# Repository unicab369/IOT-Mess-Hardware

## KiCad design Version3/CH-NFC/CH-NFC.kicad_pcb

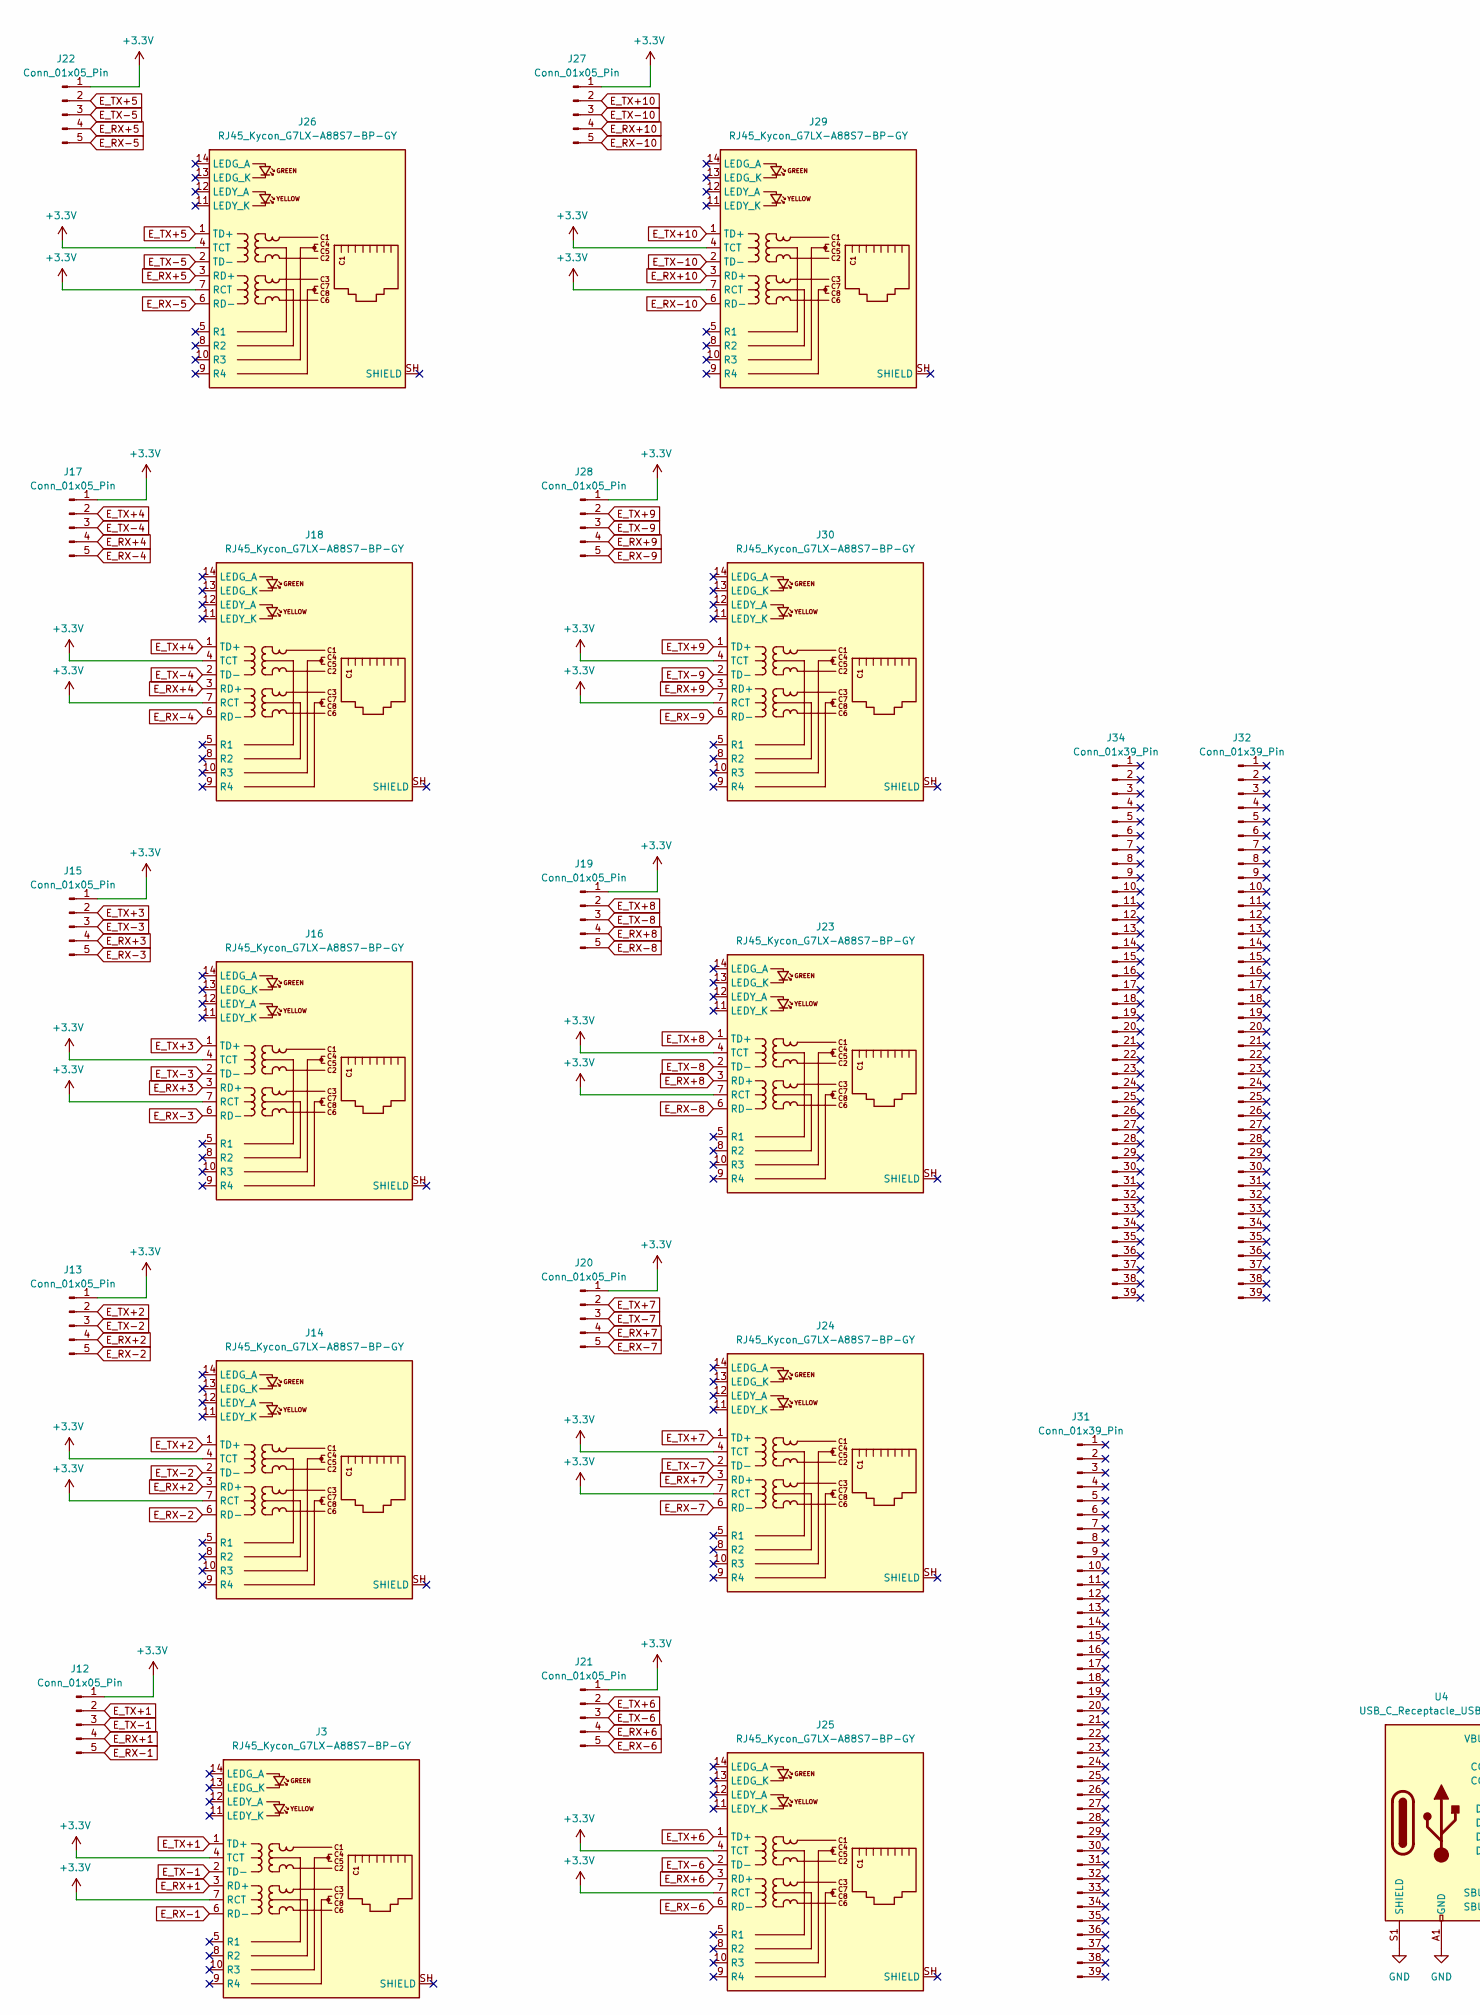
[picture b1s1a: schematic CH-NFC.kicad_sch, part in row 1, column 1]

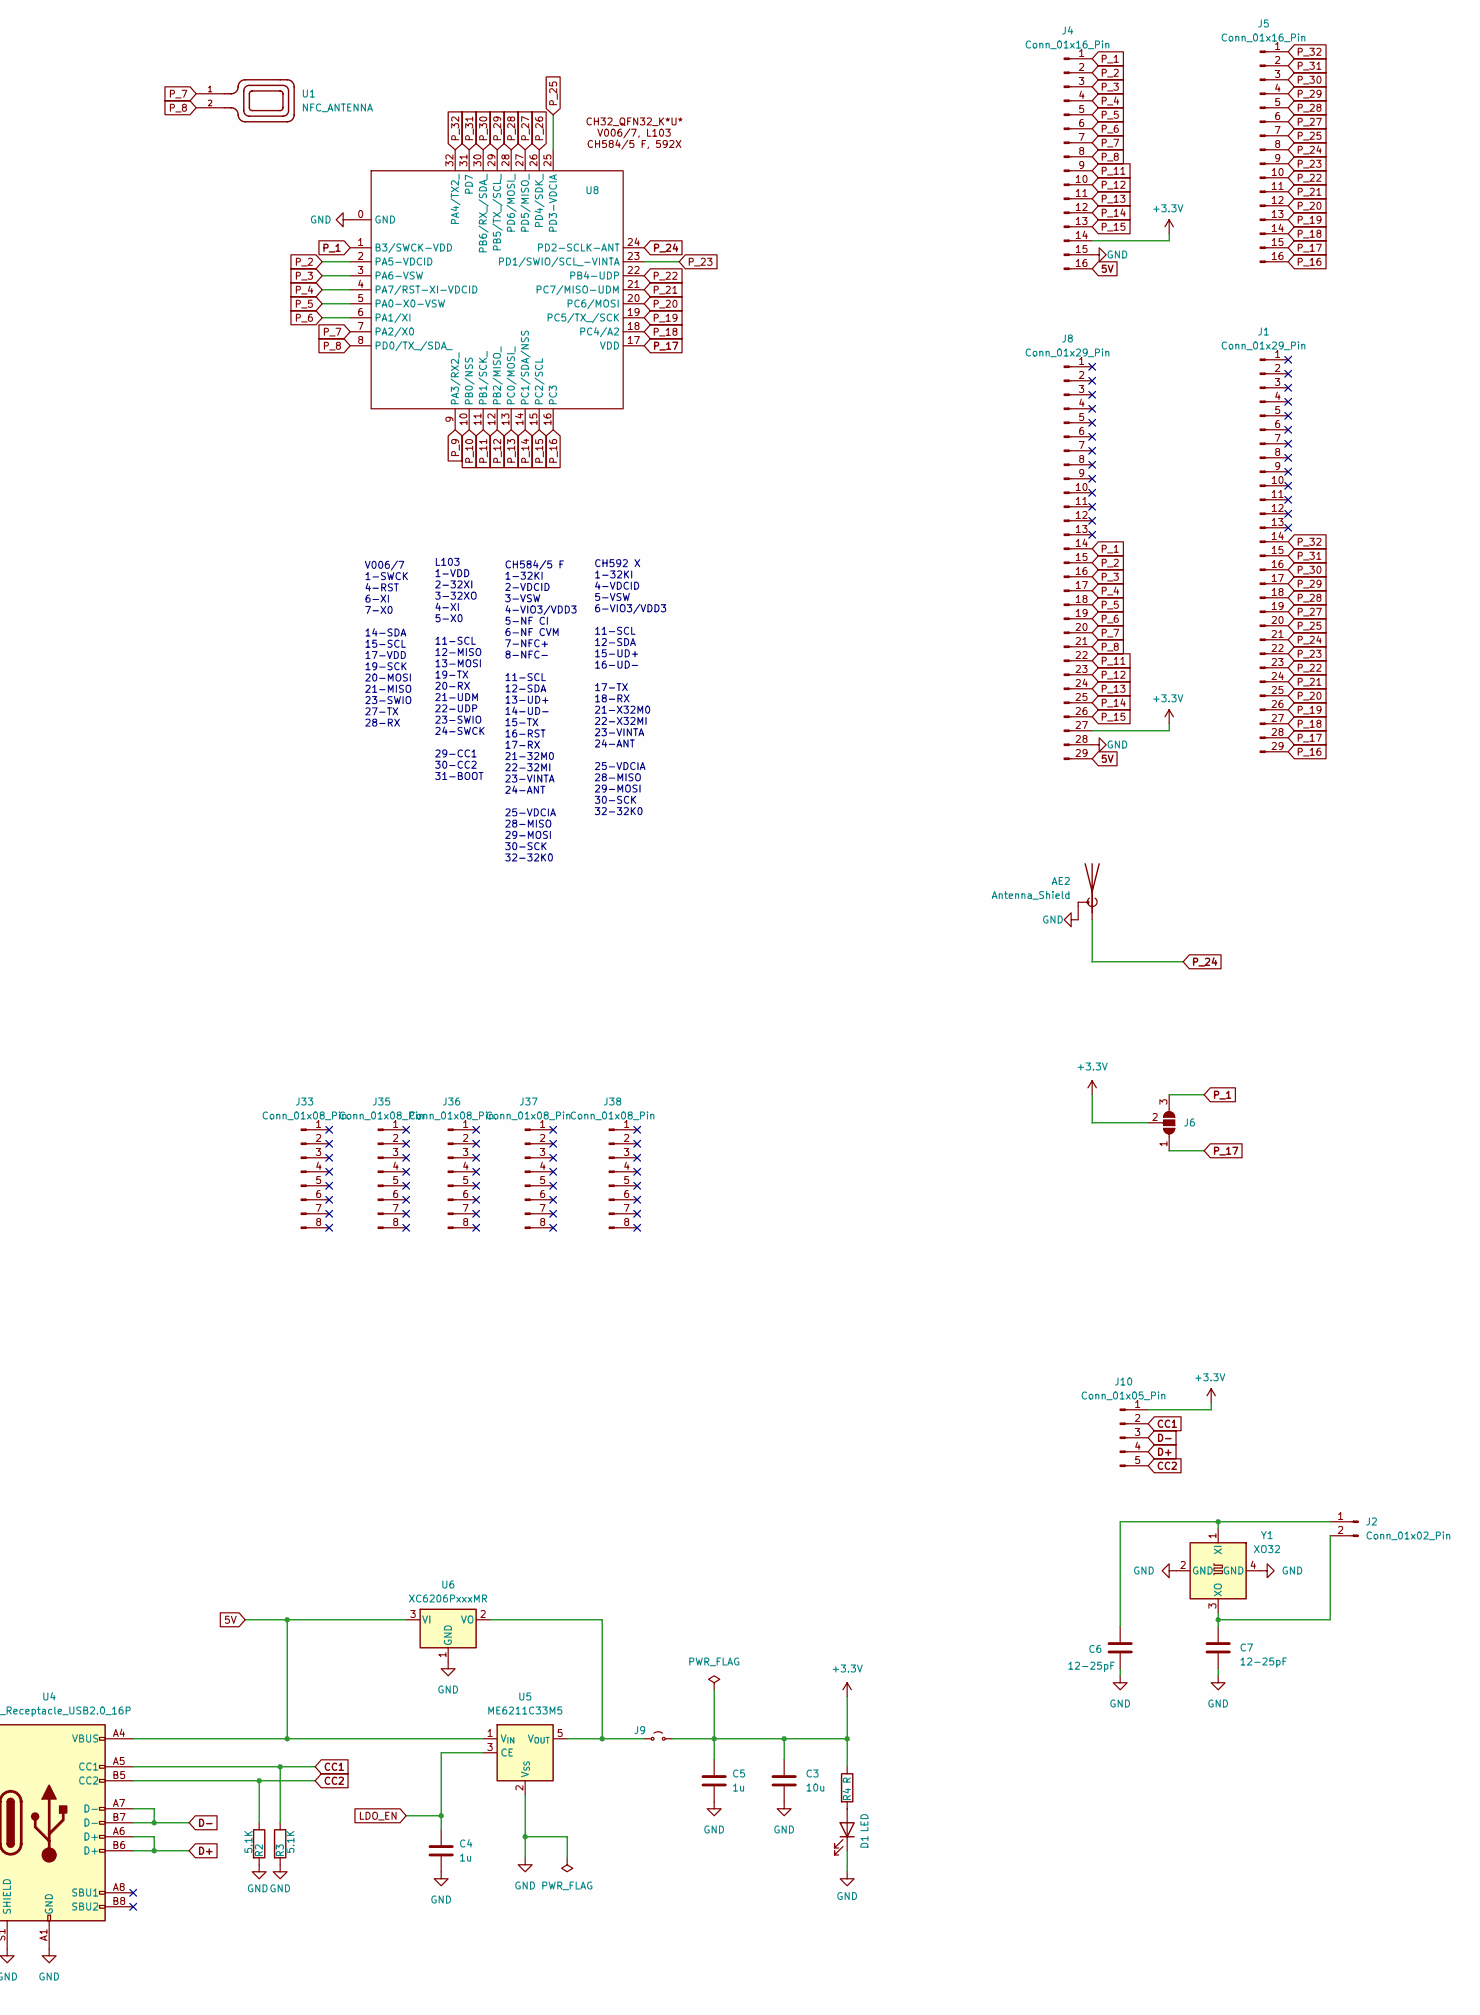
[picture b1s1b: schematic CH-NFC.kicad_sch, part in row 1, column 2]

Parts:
AE2: Antenna_Shield; Texas_SWRA117D_2.4GHz_Left
C3: 10u; C_0603_1608Metric
C4, C5: 1u; C_0603_1608Metric
C6, C7: 12-25pF; C_0603_1608Metric
D1: LED; LED_0603_1608Metric
J1, J8: Conn_01x29_Pin; PinHeader_1x29_P2.54mm_Vertical
J2: Conn_01x02_Pin; PinHeader_1x02_P1.27mm_Vertical
J3, J14, J16, J18, J23, J24, J25, J26, J29, J30: RJ45_Kycon_G7LX-A88S7-BP-GY; RJ45_Kycon_G7LX-A88S7-BP-xx_Horizontal
J4, J5: Conn_01x16_Pin; PinHeader_1x16_P2.54mm_Vertical
J6: Jumper; Jumper-3_P1.3mm_Open_RoundedPad1.0x1.5mm
J9: Jumper_2; Jumpper-triangle
J10: Conn_01x05_Pin; PinHeader_1x05_P1.27mm_Vertical
J12, J13, J15, J17, J19, J20, J21, J22, J27, J28: Conn_01x05_Pin; PinHeader_1x05_P2.54mm_Vertical
J31, J32, J34: Conn_01x39_Pin; PinHeader_1x39_P2.54mm_Vertical
J33, J35, J36, J37, J38: Conn_01x08_Pin; PinHeader_1x08_P2.54mm_Vertical
R2, R3: 5.1K; R_0603_1608Metric
R4: R; R_0603_1608Metric
U1: NFC_ANTENNA; NFC_ANT
U4: USB_C_Receptacle_USB2.0_16P; USB_C_Receptacle_HRO_TYPE-C-31-M-12
U5: ME6211C33M5; SOT-23-5
U6: XC6206PxxxMR; SOT-23-3
U8: QFN-32-1EP_4x4mm_P0.4mm_EP2.65x2.65mm_ThermalVias
Y1: XO32; Oscillator_SMD_EuroQuartz_XO32-4Pin_3.2x2.5mm

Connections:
5V: J4.16, J8.29, U4.A4 (VBUS), U4.A9 (VBUS), U4.B4 (VBUS), U4.B9 (VBUS), U5.1 (V_{IN}), U6.3 (VI)
+3.3V: C3.1, C5.1, J3.4 (TCT), J3.7 (RCT), J4.14, J6.2 (C), J8.27, J9.2 (B), J10.1, J12.1, J13.1, J14.4 (TCT), J14.7 (RCT), J15.1, J16.4 (TCT), J16.7 (RCT), J17.1, J18.4 (TCT), J18.7 (RCT), J19.1, J20.1, J21.1, J22.1, J23.4 (TCT), J23.7 (RCT), J24.4 (TCT), J24.7 (RCT), J25.4 (TCT), J25.7 (RCT), J26.4 (TCT), J26.7 (RCT), J27.1, J28.1, J29.4 (TCT), J29.7 (RCT), J30.4 (TCT), J30.7 (RCT), R4.1
CC1: J10.2, R3.1, U4.A5 (CC1)
CC2: J10.5, R2.1, U4.B5 (CC2)
D+: J10.4, U4.A6 (D+), U4.B6 (D+)
D-: J10.3, U4.A7 (D-), U4.B7 (D-)
E_RX+1: J3.3 (RD+), J12.4
E_RX+2: J13.4, J14.3 (RD+)
E_RX+3: J15.4, J16.3 (RD+)
E_RX+4: J17.4, J18.3 (RD+)
E_RX+5: J22.4, J26.3 (RD+)
E_RX+6: J21.4, J25.3 (RD+)
E_RX+7: J20.4, J24.3 (RD+)
E_RX+8: J19.4, J23.3 (RD+)
E_RX+9: J28.4, J30.3 (RD+)
E_RX+10: J27.4, J29.3 (RD+)
E_RX-1: J3.6 (RD-), J12.5
E_RX-2: J13.5, J14.6 (RD-)
E_RX-3: J15.5, J16.6 (RD-)
E_RX-4: J17.5, J18.6 (RD-)
E_RX-5: J22.5, J26.6 (RD-)
E_RX-6: J21.5, J25.6 (RD-)
E_RX-7: J20.5, J24.6 (RD-)
E_RX-8: J19.5, J23.6 (RD-)
E_RX-9: J28.5, J30.6 (RD-)
E_RX-10: J27.5, J29.6 (RD-)
E_TX+1: J3.1 (TD+), J12.2
E_TX+2: J13.2, J14.1 (TD+)
E_TX+3: J15.2, J16.1 (TD+)
E_TX+4: J17.2, J18.1 (TD+)
E_TX+5: J22.2, J26.1 (TD+)
E_TX+6: J21.2, J25.1 (TD+)
E_TX+7: J20.2, J24.1 (TD+)
E_TX+8: J19.2, J23.1 (TD+)
E_TX+9: J28.2, J30.1 (TD+)
E_TX+10: J27.2, J29.1 (TD+)
E_TX-1: J3.2 (TD-), J12.3
E_TX-2: J13.3, J14.2 (TD-)
E_TX-3: J15.3, J16.2 (TD-)
E_TX-4: J17.3, J18.2 (TD-)
E_TX-5: J22.3, J26.2 (TD-)
E_TX-6: J21.3, J25.2 (TD-)
E_TX-7: J20.3, J24.2 (TD-)
E_TX-8: J19.3, J23.2 (TD-)
E_TX-9: J28.3, J30.2 (TD-)
E_TX-10: J27.3, J29.2 (TD-)
GND: AE2.2 (Shield), C3.2, C4.2, C5.2, C6.2, C7.2, D1.1 (K), J4.15, J8.28, R2.2, R3.2, U4.A1 (GND), U4.A12 (GND), U4.B1 (GND), U4.B12 (GND), U4.S1 (SHIELD), U5.2 (V_{SS}), U6.1 (GND), U8.0 (GND), Y1.2 (GND), Y1.4 (GND)
LDO_EN: C4.1, U5.3 (CE)
unnamed: D1.2 (A), R4.2
unnamed: C6.1, J2.1, Y1.1 (XI)
unnamed: C7.1, J2.2, Y1.3 (XO)
unnamed: J9.1 (A), U5.5 (V_{OUT}), U6.2 (VO)
P_1: J4.1, J6.3 (B), J8.14, U8.1 (B3/SWCK-VDD)
P_2: J4.2, J8.15, U8.2 (PA5-VDCID)
P_3: J4.3, J8.16, U8.3 (PA6-VSW)
P_4: J4.4, J8.17, U8.4 (PA7/RST-XI-VDCID)
P_5: J4.5, J8.18, U8.5 (PA0-X0-VSW)
P_6: J4.6, J8.19, U8.6 (PA1/XI)
P_7: J4.7, J8.20, U1.1, U8.7 (PA2/X0)
P_8: J4.8, J8.21, U1.2, U8.8 (PD0/TX_/SDA_)
P_9: U8.9 (PA3/RX2_)
P_10: U8.10 (PB0/NSS)
P_11: J4.9, J8.22, U8.11 (PB1/SCK_)
P_12: J4.10, J8.23, U8.12 (PB2/MISO_)
P_13: J4.11, J8.24, U8.13 (PC0/MOSI_)
P_14: J4.12, J8.25, U8.14 (PC1/SDA/NSS)
P_15: J4.13, J8.26, U8.15 (PC2/SCL)
P_16: J1.29, J5.16, U8.16 (PC3)
P_17: J1.28, J5.15, J6.1 (A), U8.17 (VDD)
P_18: J1.27, J5.14, U8.18 (PC4/A2)
P_19: J1.26, J5.13, U8.19 (PC5/TX_/SCK)
P_20: J1.25, J5.12, U8.20 (PC6/MOSI)
P_21: J1.24, J5.11, U8.21 (PC7/MISO-UDM)
P_22: J1.23, J5.10, U8.22 (PB4-UDP)
P_23: J1.22, J5.9, U8.23 (PD1/SWIO/SCL_-VINTA)
P_24: AE2.1 (A), J1.21, J5.8, U8.24 (PD2-SCLK-ANT)
P_25: J1.20, J5.7, U8.25 (PD3-VDCIA)
P_26: U8.26 (PD4/SDK_)
P_27: J1.19, J5.6, U8.27 (PD5/MISO_)
P_28: J1.18, J5.5, U8.28 (PD6/MOSI_)
P_29: J1.17, J5.4, U8.29 (PB5/TX_/SCL_)
P_30: J1.16, J5.3, U8.30 (PB6/RX_/SDA_)
P_31: J1.15, J5.2, U8.31 (PD7)
P_32: J1.14, J5.1, U8.32 (PA4/TX2_)

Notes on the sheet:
V006/7 1-SWCK 4-RST 6-XI 7-X0 14-SDA 15-SCL 17-VDD 19-SCK 20-MOSI 21-MISO 23-SWIO 27-TX 28-RX
L103 1-VDD 2-32XI 3-32XO 4-XI 5-X0 11-SCL 12-MISO 13-MOSI 19-TX 20-RX 21-UDM 22-UDP 23-SWIO 24-SWCK 29-CC1 30-CC2 31-BOOT
CH592 X 1-32KI 4-VDCID 5-VSW 6-VIO3/VDD3 11-SCL 12-SDA 15-UD+ 16-UD- 17-TX 18-RX 21-X32M0 22-X32MI 23-VINTA 24-ANT 25-VDCIA 28-MISO 29-MOSI 30-SCK 32-32K0
CH584/5 F 1-32KI 2-VDCID 3-VSW 4-VIO3/VDD3 5-NF CI 6-NF CVM 7-NFC+ 8-NFC- 11-SCL 12-SDA 13-UD+ 14-UD- 15-TX 16-RST 17-RX 21-32M0 22-32MI 23-VINTA 24-ANT 25-VDCIA 28-MISO 29-MOSI 30-SCK 32-32K0

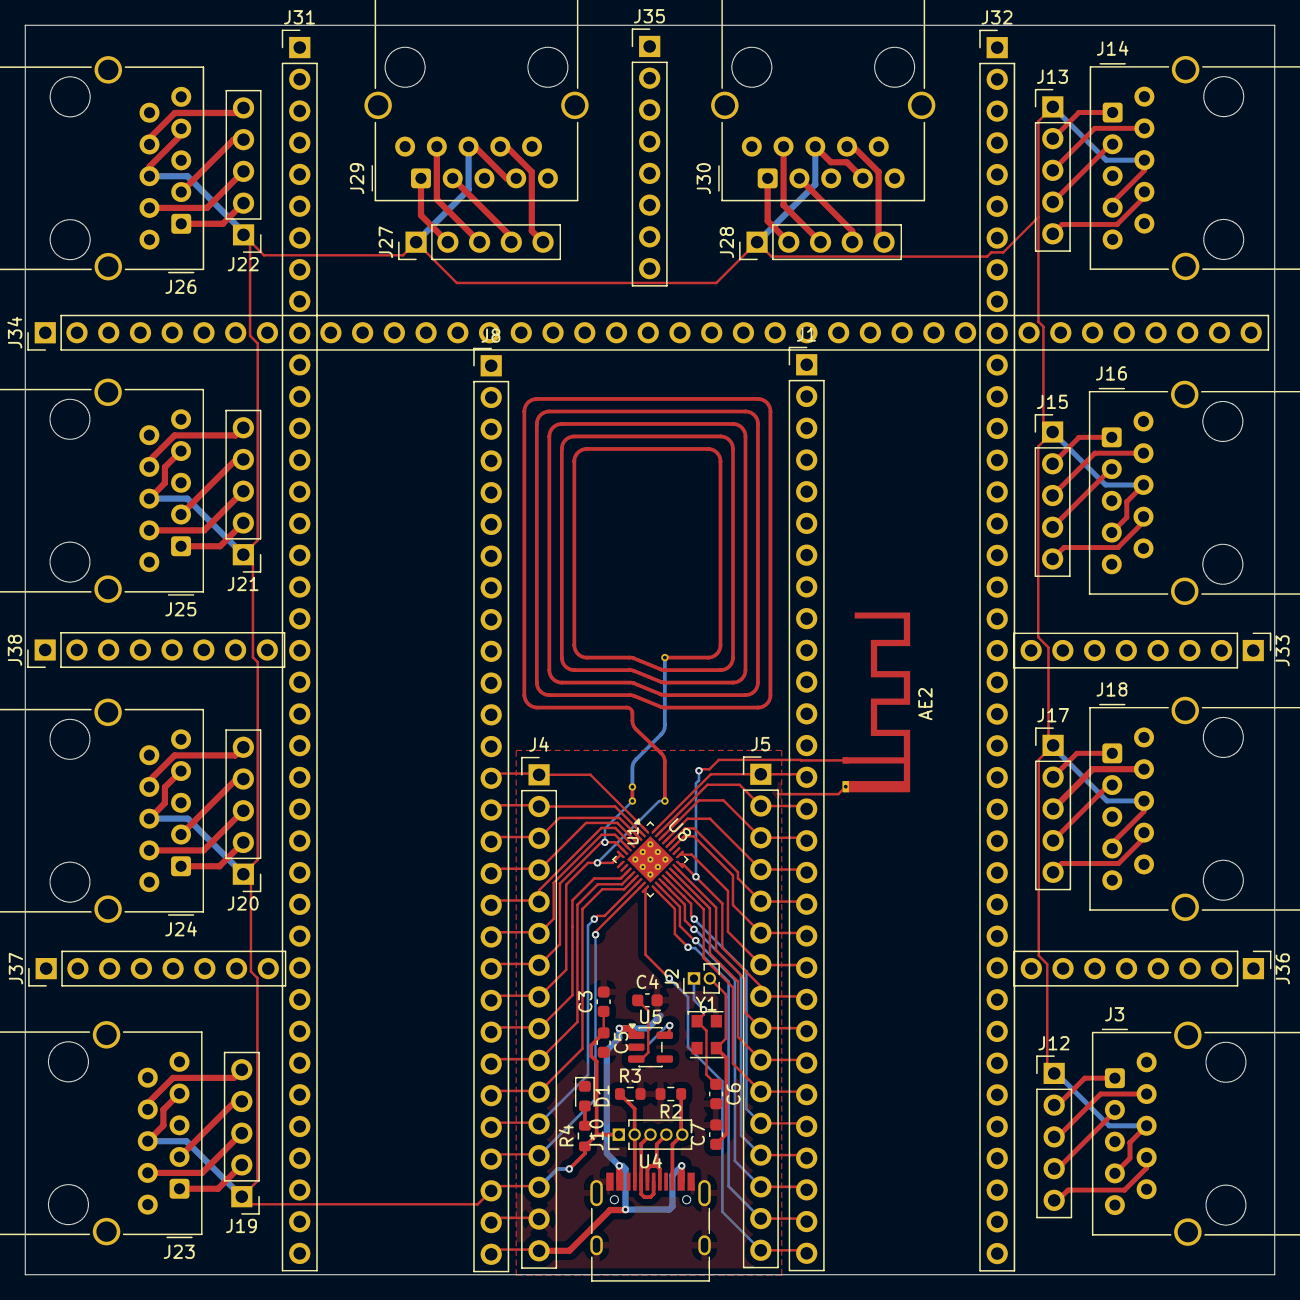
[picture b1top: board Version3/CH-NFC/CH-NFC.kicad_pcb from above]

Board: 2 copper layers, 100.0 x 100.0 mm, 50 parts (1 on the bottom side), 81 nets.

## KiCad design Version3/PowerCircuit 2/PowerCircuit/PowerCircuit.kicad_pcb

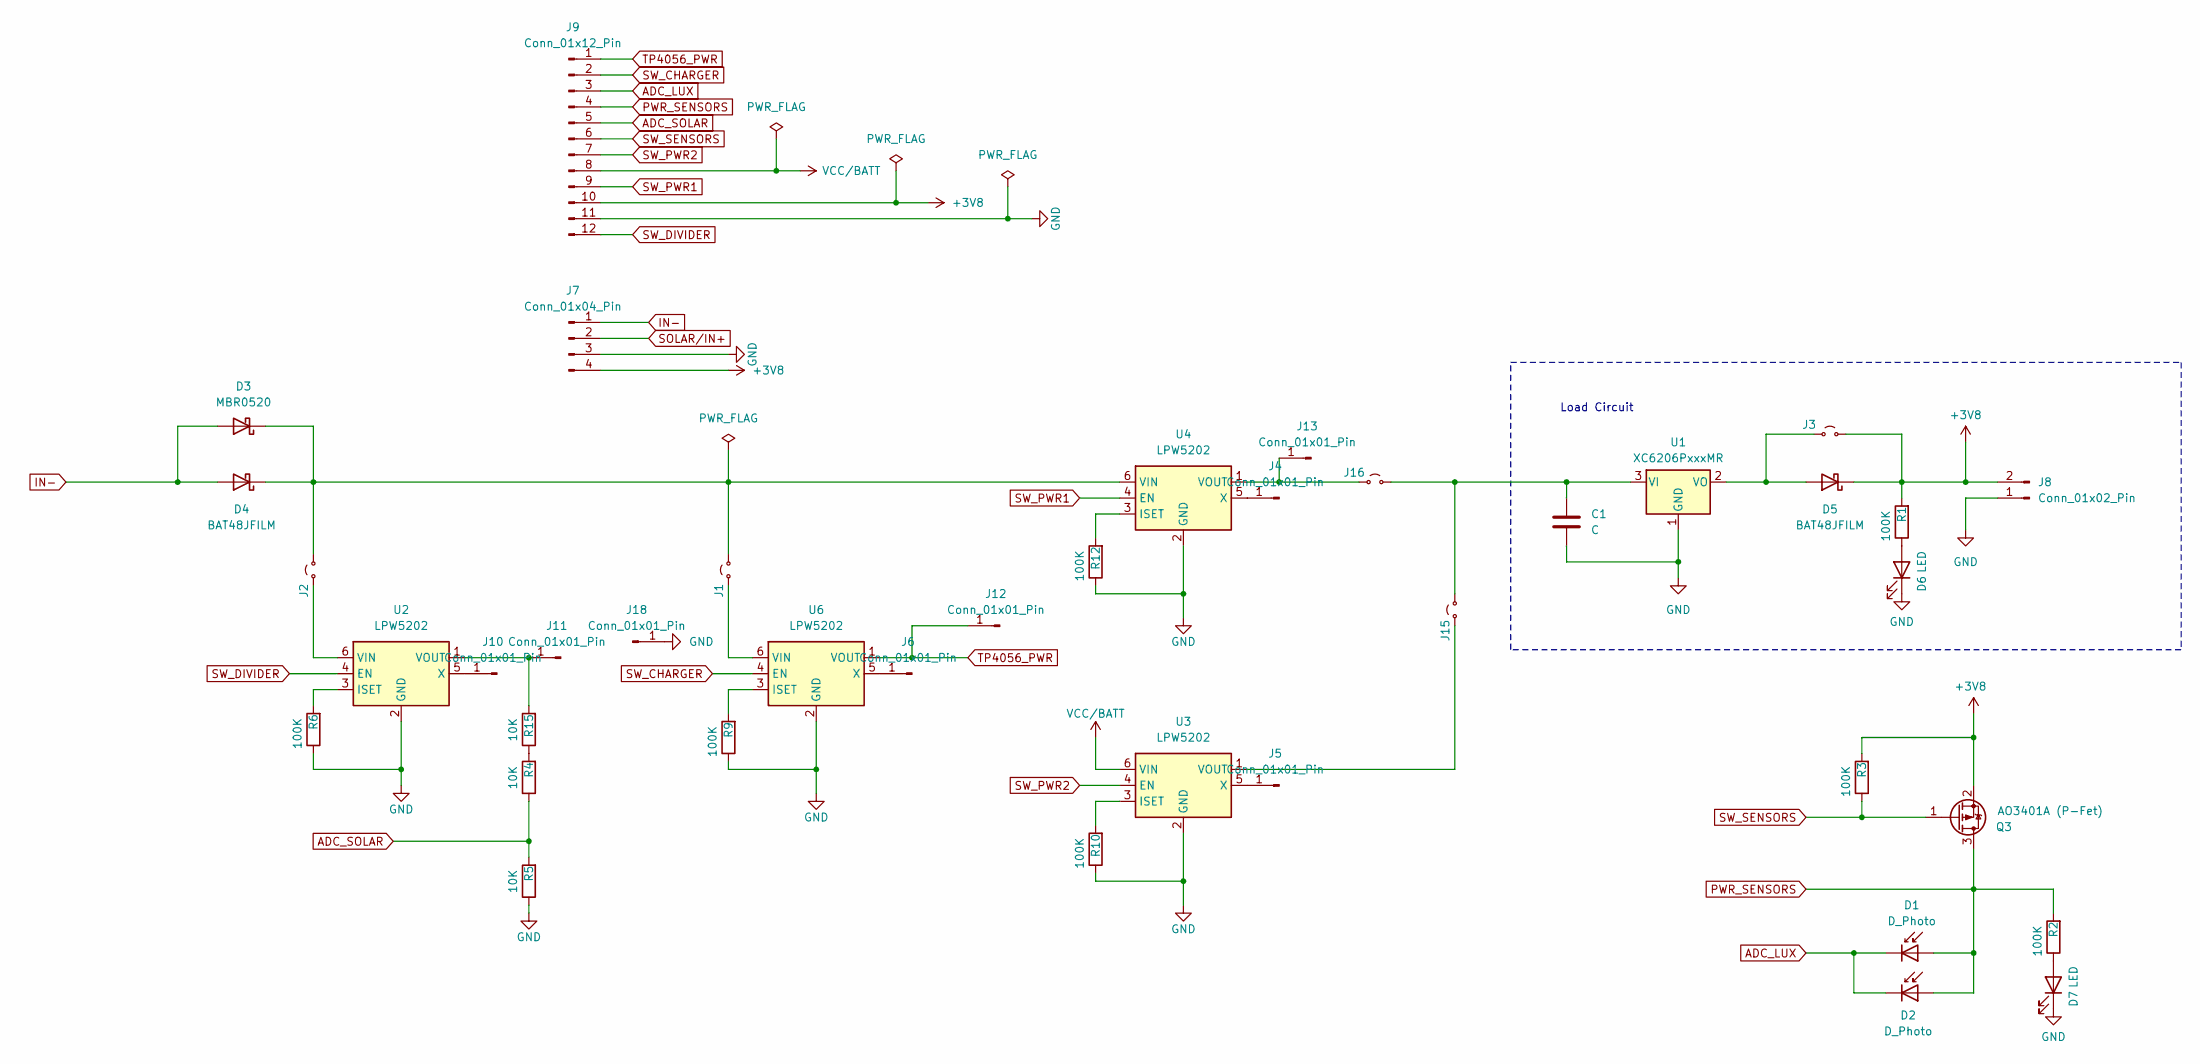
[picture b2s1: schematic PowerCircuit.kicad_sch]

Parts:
C1: C; C_0603_1608Metric
D1: D_Photo; LED_0603_1608Metric
D2: D_Photo; LED_0805_2012Metric
D3: MBR0520; D_SOD-123
D4, D5: BAT48JFILM; D_SOD-323
D6, D7: LED; LED_0805_2012Metric
J1, J2, J3, J15, J16: Jumper_2; Jumper-triangle
J4, J5, J6, J10, J11, J12, J13: Conn_01x01_Pin; PinHeader_1x01_P1.00mm_Vertical
J7: Conn_01x04_Pin; PinHeader_1x04_P2.54mm_Vertical
J8: Conn_01x02_Pin; PinHeader_1x02_P1.00mm_Vertical
J9: Conn_01x12_Pin; PinHeader_1x12_P2.54mm_Vertical
J18: Conn_01x01_Pin; PinHeader_1x01_P2.54mm_Vertical
Q3: AO3401A (P-Fet); SOT-23
R1, R2, R3, R6, R9, R10, R12: 100K; R_0805_2012Metric
R4, R5, R15: 10K; R_0805_2012Metric
U1: XC6206PxxxMR; SOT-23-3
U2, U3, U4, U6: LPW5202; SOT-23-6

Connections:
+3V8: D5.1 (K), J3.2 (B), J7.4, J8.2, J9.10, Q3.2 (S), R1.2, R3.2
ADC_LUX: D1.1 (K), D2.1 (K), J9.3
ADC_SOLAR: J9.5, R4.1, R5.2
GND: C1.2, D6.1 (K), D7.1 (K), J7.3, J8.1, J9.11, J18.1, R5.1, R6.1, R9.1, R10.1, R12.1, U1.1 (GND), U2.2 (GND), U3.2 (GND), U4.2 (GND), U6.2 (GND)
IN-: D3.2 (A), D4.2 (A), J7.1
unnamed: D3.1 (K), D4.1 (K), J1.2 (B), J2.2 (B), U4.6 (VIN)
unnamed: D5.2 (A), J3.1 (A), U1.2 (VO)
unnamed: D6.2 (A), R1.1
unnamed: D7.2 (A), R2.1
unnamed: J1.1 (A), U6.6 (VIN)
unnamed: J2.1 (A), U2.6 (VIN)
unnamed: J4.1, U4.5 (X)
unnamed: J5.1, U3.5 (X)
unnamed: J6.1, U6.5 (X)
unnamed: J10.1, U2.5 (X)
unnamed: J11.1, R15.2, U2.1 (VOUT)
unnamed: J13.1, J16.1 (A), U4.1 (VOUT)
unnamed: J15.1 (A), U3.1 (VOUT)
unnamed: C1.1, J15.2 (B), J16.2 (B), U1.3 (VI)
unnamed: R4.2, R15.1
unnamed: R6.2, U2.3 (ISET)
unnamed: R10.2, U3.3 (ISET)
unnamed: R12.2, U4.3 (ISET)
unnamed: R9.2, U6.3 (ISET)
PWR_SENSORS: D1.2 (A), D2.2 (A), J9.4, Q3.3 (D), R2.2
SOLAR/IN+: J7.2
SW_CHARGER: J9.2, U6.4 (EN)
SW_DIVIDER: J9.12, U2.4 (EN)
SW_PWR1: J9.9, U4.4 (EN)
SW_PWR2: J9.7, U3.4 (EN)
SW_SENSORS: J9.6, Q3.1 (G), R3.1
TP4056_PWR: J9.1, J12.1, U6.1 (VOUT)
VCC/BATT: J9.8, U3.6 (VIN)

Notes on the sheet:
Load Circuit

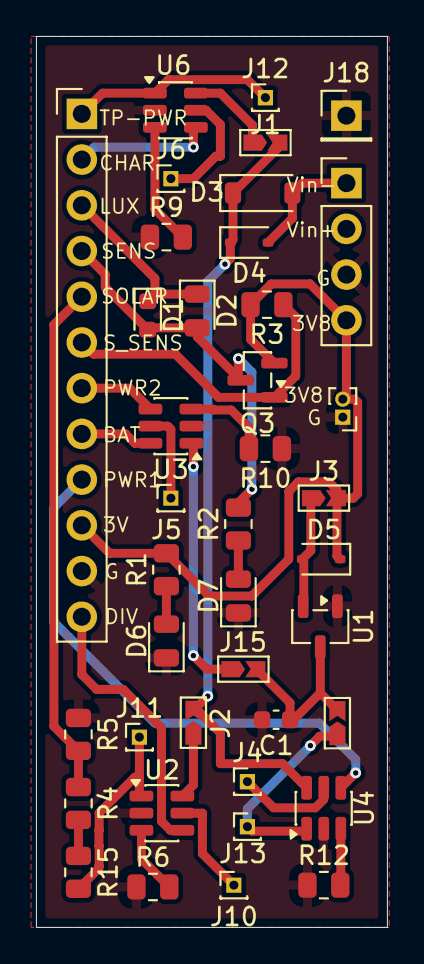
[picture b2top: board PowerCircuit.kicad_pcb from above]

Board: 2 copper layers, 19.5 x 49.5 mm, 40 parts (0 on the bottom side), 32 nets.

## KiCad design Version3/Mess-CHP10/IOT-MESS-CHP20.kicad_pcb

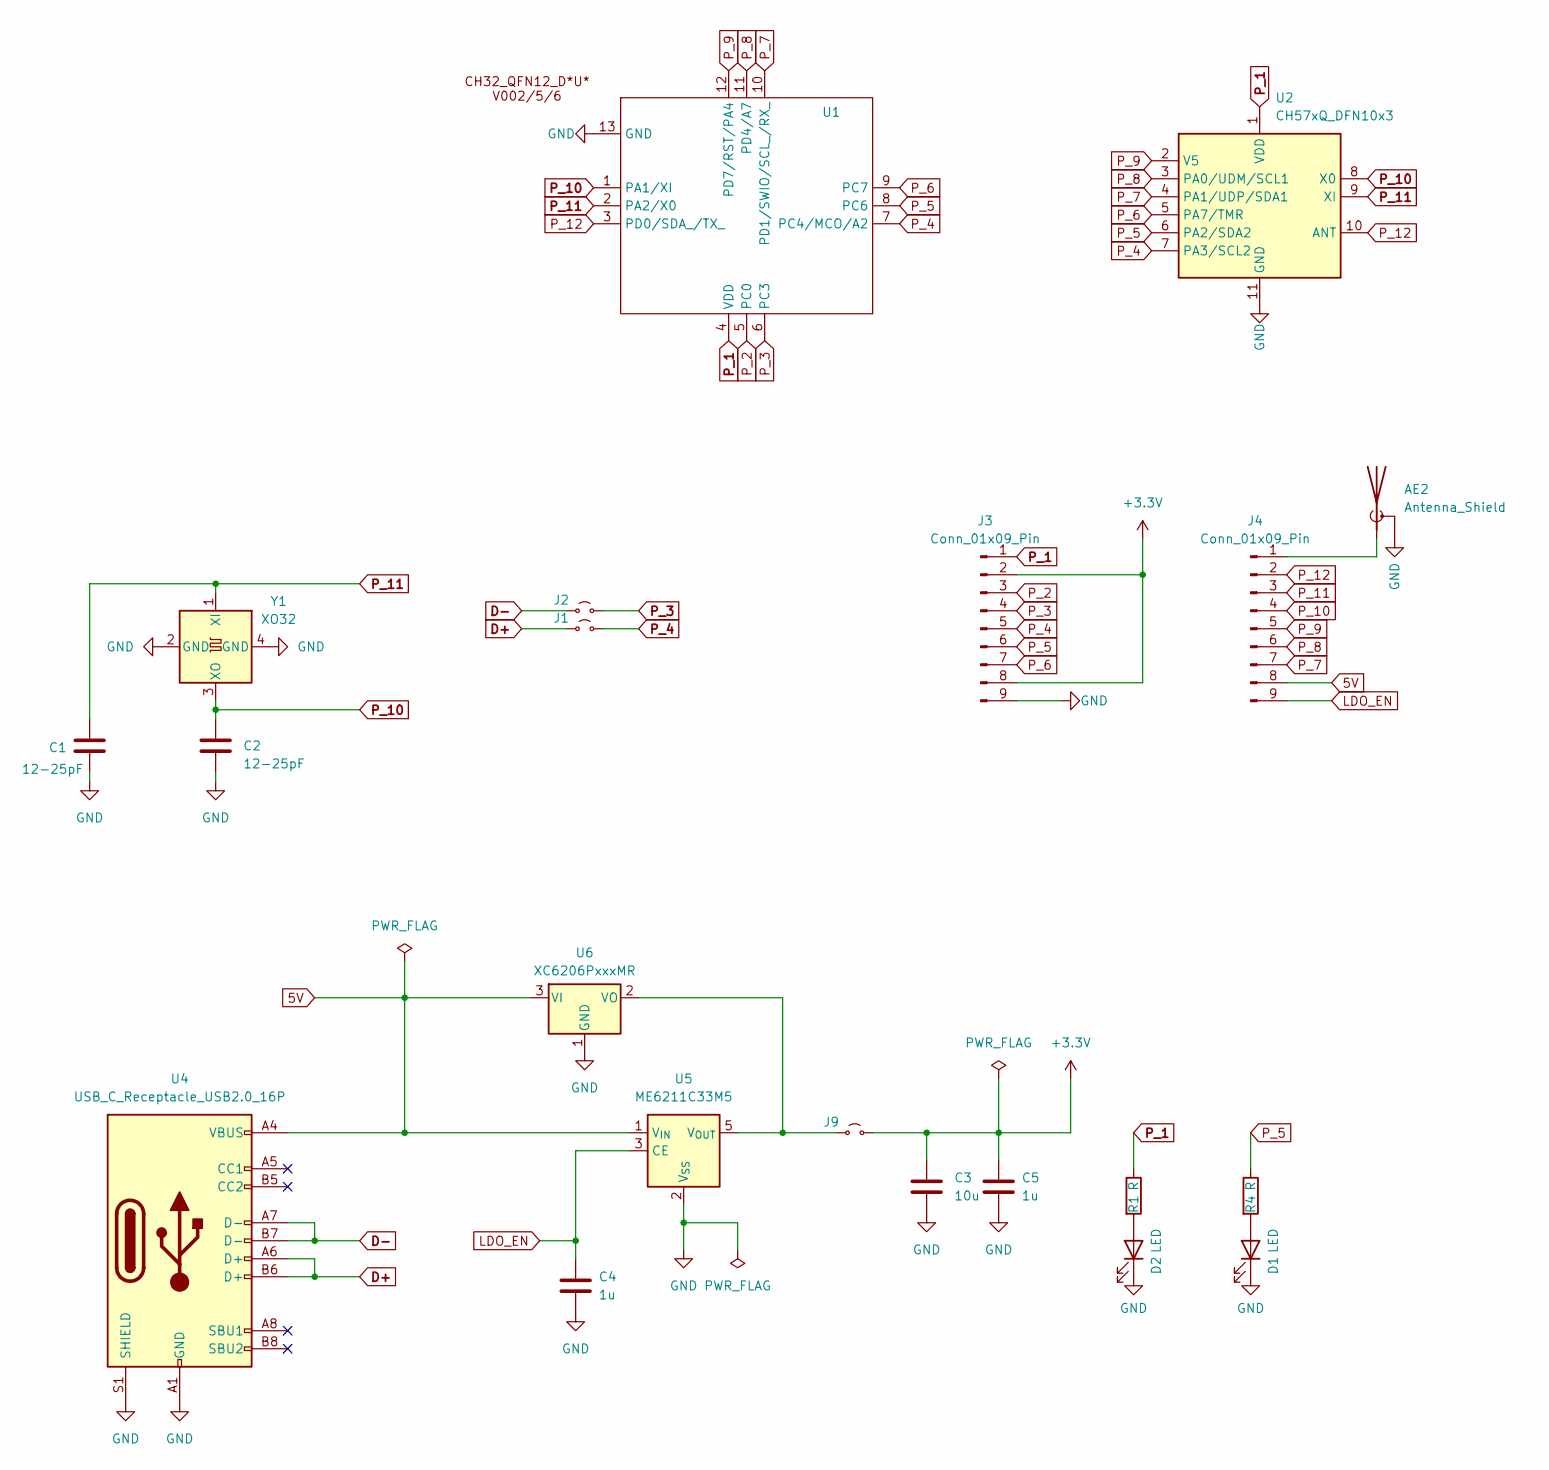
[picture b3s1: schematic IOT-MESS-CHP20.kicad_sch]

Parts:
AE2: Antenna_Shield; Texas_SWRA117D_2.4GHz_Left
C1, C2: 12-25pF; C_0603_1608Metric
C3: 10u; C_0603_1608Metric
C4, C5: 1u; C_0603_1608Metric
D1, D2: LED; LED_0603_1608Metric
J1, J2, J9: Jumper_2; Jumper-triangle
J3, J4: Conn_01x09_Pin; PinSocket_1x09_P2.54mm_Vertical
R1, R4: R; R_0603_1608Metric
U1: UQFN-12-1EP_2x2mm_P0.4mm_EP1.1x1.1mm
U2: CH57xQ_DFN10x3; DFN10x3
U4: USB_C_Receptacle_USB2.0_16P; USB_C_Receptacle_HRO_TYPE-C-31-M-12
U5: ME6211C33M5; SOT-23-5
U6: XC6206PxxxMR; SOT-23-3
Y1: XO32; Oscillator_SMD_EuroQuartz_XO32-4Pin_3.2x2.5mm

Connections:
5V: J4.8, U4.A4 (VBUS), U4.A9 (VBUS), U4.B4 (VBUS), U4.B9 (VBUS), U5.1 (V_{IN}), U6.3 (VI)
+3.3V: C3.1, C5.1, J3.2, J3.8, J9.2 (B)
D+: J1.1 (A), U4.A6 (D+), U4.B6 (D+)
D-: J2.1 (A), U4.A7 (D-), U4.B7 (D-)
GND: AE2.2 (Shield), C1.2, C2.2, C3.2, C4.2, C5.2, D1.1 (K), D2.1 (K), J3.9, U1.13 (GND), U2.11 (GND), U4.A1 (GND), U4.A12 (GND), U4.B1 (GND), U4.B12 (GND), U4.S1 (SHIELD), U5.2 (V_{SS}), U6.1 (GND), Y1.2 (GND), Y1.4 (GND)
LDO_EN: C4.1, J4.9, U5.3 (CE)
unnamed: AE2.1 (A), J4.1
unnamed: D1.2 (A), R4.2
unnamed: D2.2 (A), R1.2
unnamed: J9.1 (A), U5.5 (V_{OUT}), U6.2 (VO)
P_1: J3.1, R1.1, U1.4 (VDD), U2.1 (VDD)
P_2: J3.3, U1.5 (PC0)
P_3: J2.2 (B), J3.4, U1.6 (PC3)
P_4: J1.2 (B), J3.5, U1.7 (PC4/MCO/A2), U2.7 (PA3/SCL2)
P_5: J3.6, R4.1, U1.8 (PC6), U2.6 (PA2/SDA2)
P_6: J3.7, U1.9 (PC7), U2.5 (PA7/TMR)
P_7: J4.7, U1.10 (PD1/SWIO/SCL_/RX_), U2.4 (PA1/UDP/SDA1)
P_8: J4.6, U1.11 (PD4/A7), U2.3 (PA0/UDM/SCL1)
P_9: J4.5, U1.12 (PD7/RST/PA4), U2.2 (V5)
P_10: C2.1, J4.4, U1.1 (PA1/XI), U2.8 (X0), Y1.3 (XO)
P_11: C1.1, J4.3, U1.2 (PA2/X0), U2.9 (XI), Y1.1 (XI)
P_12: J4.2, U1.3 (PD0/SDA_/TX_), U2.10 (ANT)

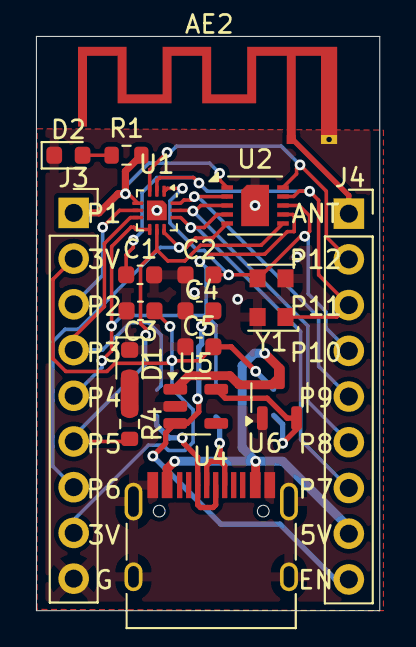
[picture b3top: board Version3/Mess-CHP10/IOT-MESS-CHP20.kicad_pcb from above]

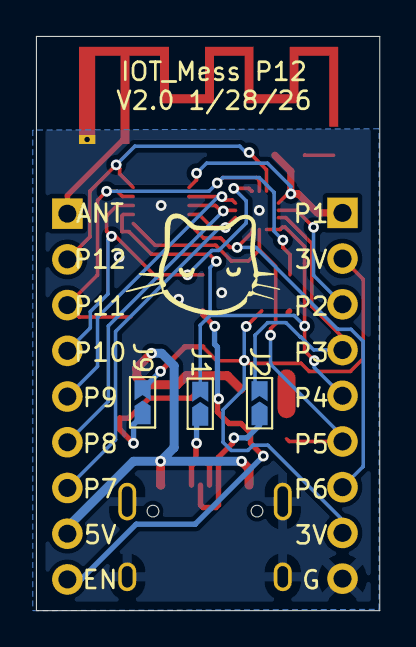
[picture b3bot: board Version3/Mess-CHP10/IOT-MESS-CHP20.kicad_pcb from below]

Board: 2 copper layers, 19.1 x 31.9 mm, 21 parts (3 on the bottom side), 22 nets.
